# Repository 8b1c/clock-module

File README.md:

# clock-module

## Demo

https://github.com/user-attachments/assets/6f4d9207-cf31-4d4b-aec3-0dd87077b01e

## Clock Module Views

### Front View

### Back View

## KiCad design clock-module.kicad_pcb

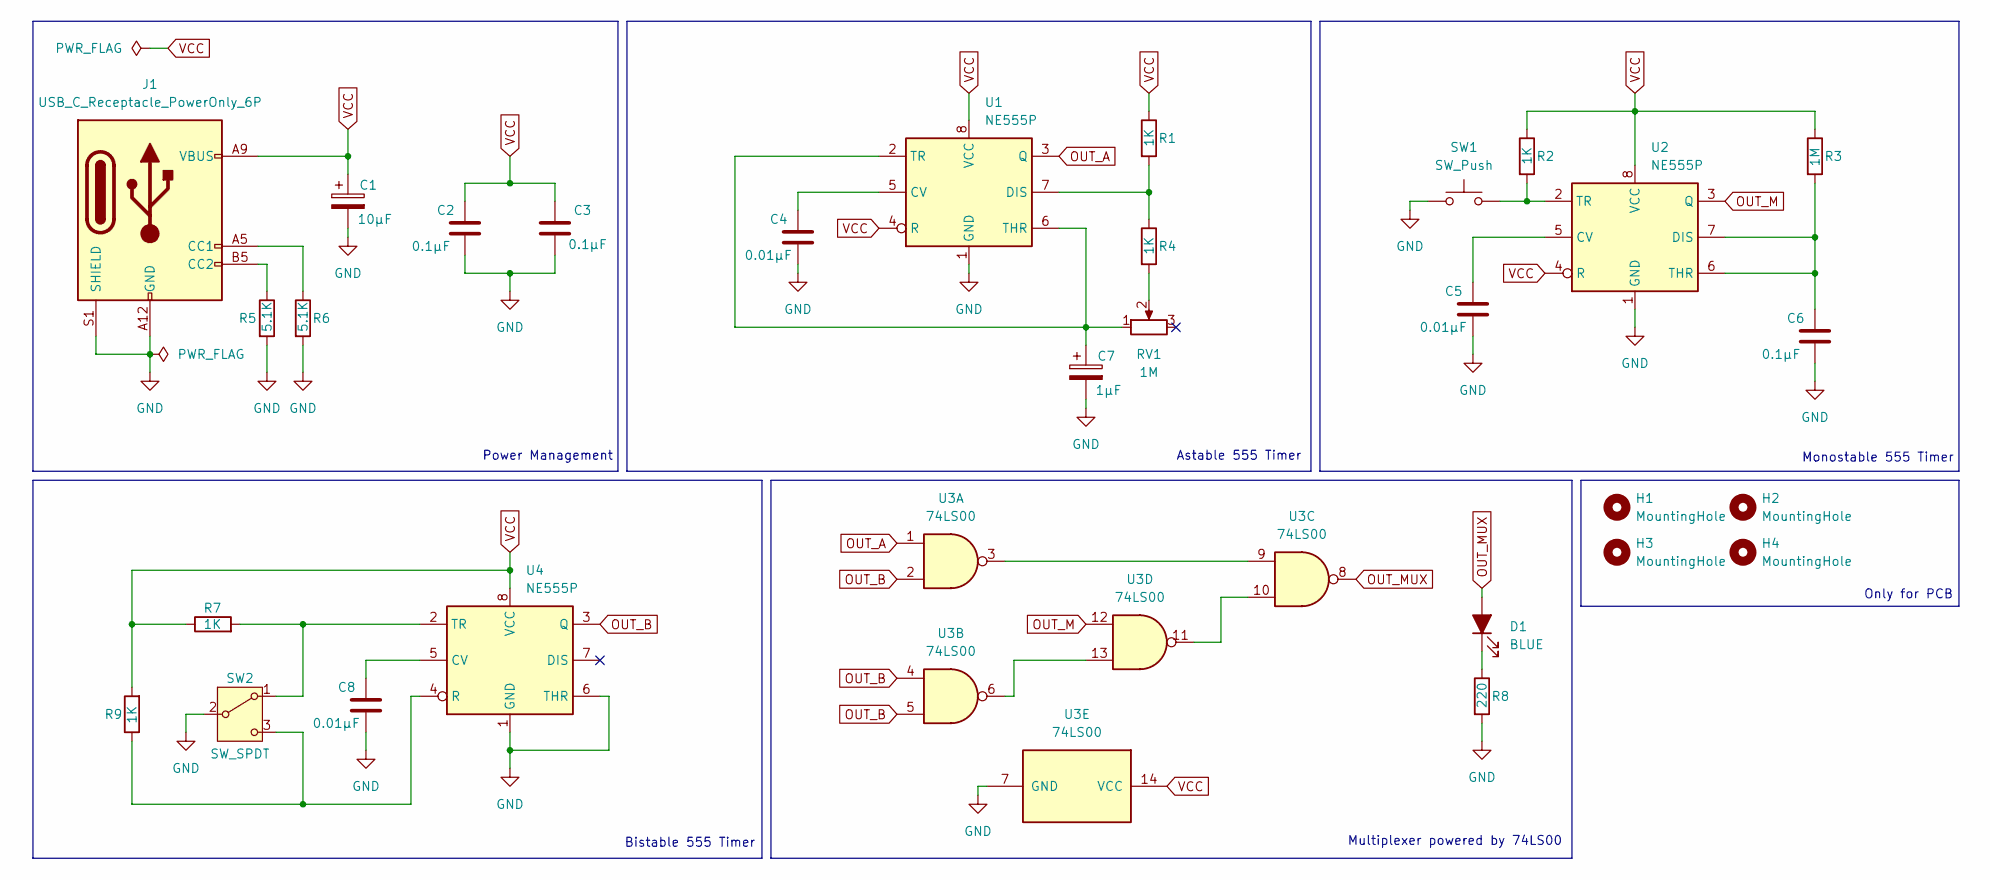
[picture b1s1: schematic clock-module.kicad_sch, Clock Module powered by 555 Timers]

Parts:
C1: 10µF; CP_Radial_D5.0mm_P2.00mm
C2, C3, C6: 0.1µF; C_Disc_D4.3mm_W1.9mm_P5.00mm
C4, C5, C8: 0.01µF; C_Disc_D4.3mm_W1.9mm_P5.00mm
C7: 1µF; CP_Radial_D5.0mm_P2.00mm
D1: BLUE; LED_D5.0mm
H1, H2, H3, H4: MountingHole; MountingHole_3.2mm_M3
J1: USB_C_Receptacle_PowerOnly_6P; USB_C_Receptacle_GCT_USB4135-GF-A_6P_TopMnt_Horizontal
R1, R2, R4, R7, R9: 1K; R_Axial_DIN0207_L6.3mm_D2.5mm_P7.62mm_Horizontal
R3: 1M; R_Axial_DIN0207_L6.3mm_D2.5mm_P7.62mm_Horizontal
R5, R6: 5.1K; R_Axial_DIN0207_L6.3mm_D2.5mm_P7.62mm_Horizontal
R8: 220; R_Axial_DIN0207_L6.3mm_D2.5mm_P7.62mm_Horizontal
RV1: 1M; Potentiometer_Bourns_PTV09A-1_Single_Vertical
SW1: SW_Push; SW_PUSH_6mm_H5mm
SW2: SW_SPDT; DPDT-pushbutton
U1, U2, U4: NE555P; DIP-8_W7.62mm
U3: 74LS00; DIP-14_W7.62mm

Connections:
GND: C1.2, C2.2, C3.2, C4.2, C5.2, C6.2, C7.2, C8.2, J1.A12 (GND), J1.B12 (GND), J1.S1 (SHIELD), R5.2, R6.2, R8.2, SW1.1, SW2.2 (B), U1.1 (GND), U2.1 (GND), U3.7 (GND), U4.1 (GND), U4.6 (THR)
unnamed: D1.1 (K), R8.1
unnamed: J1.A5 (CC1), R6.1
unnamed: J1.B5 (CC2), R5.1
unnamed: R4.2, RV1.2
unnamed: R7.2, SW2.1 (A), U4.2 (TR)
unnamed: R9.1, SW2.3 (C), U4.4 (R)
unnamed: C4.1, U1.5 (CV)
unnamed: R1.2, R4.1, U1.7 (DIS)
unnamed: C7.1, RV1.1, U1.2 (TR), U1.6 (THR)
unnamed: C5.1, U2.5 (CV)
unnamed: C6.1, R3.2, U2.6 (THR), U2.7 (DIS)
unnamed: R2.2, SW1.2, U2.2 (TR)
unnamed: U3.3, U3.9
unnamed: U3.10, U3.11
unnamed: U3.6, U3.13
unnamed: C8.1, U4.5 (CV)
OUT_A: U1.3 (Q), U3.1
OUT_B: U3.2, U3.4, U3.5, U4.3 (Q)
OUT_M: U2.3 (Q), U3.12
OUT_MUX: D1.2 (A), U3.8
VCC: C1.1, C2.1, C3.1, J1.A9 (VBUS), J1.B9 (VBUS), R1.1, R2.1, R3.1, R7.1, R9.2, U1.4 (R), U1.8 (VCC), U2.4 (R), U2.8 (VCC), U3.14 (VCC), U4.8 (VCC)

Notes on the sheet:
Power Management
Bistable 555 Timer
Only for PCB
Multiplexer powered by 74LS00
Monostable 555 Timer
Astable 555 Timer

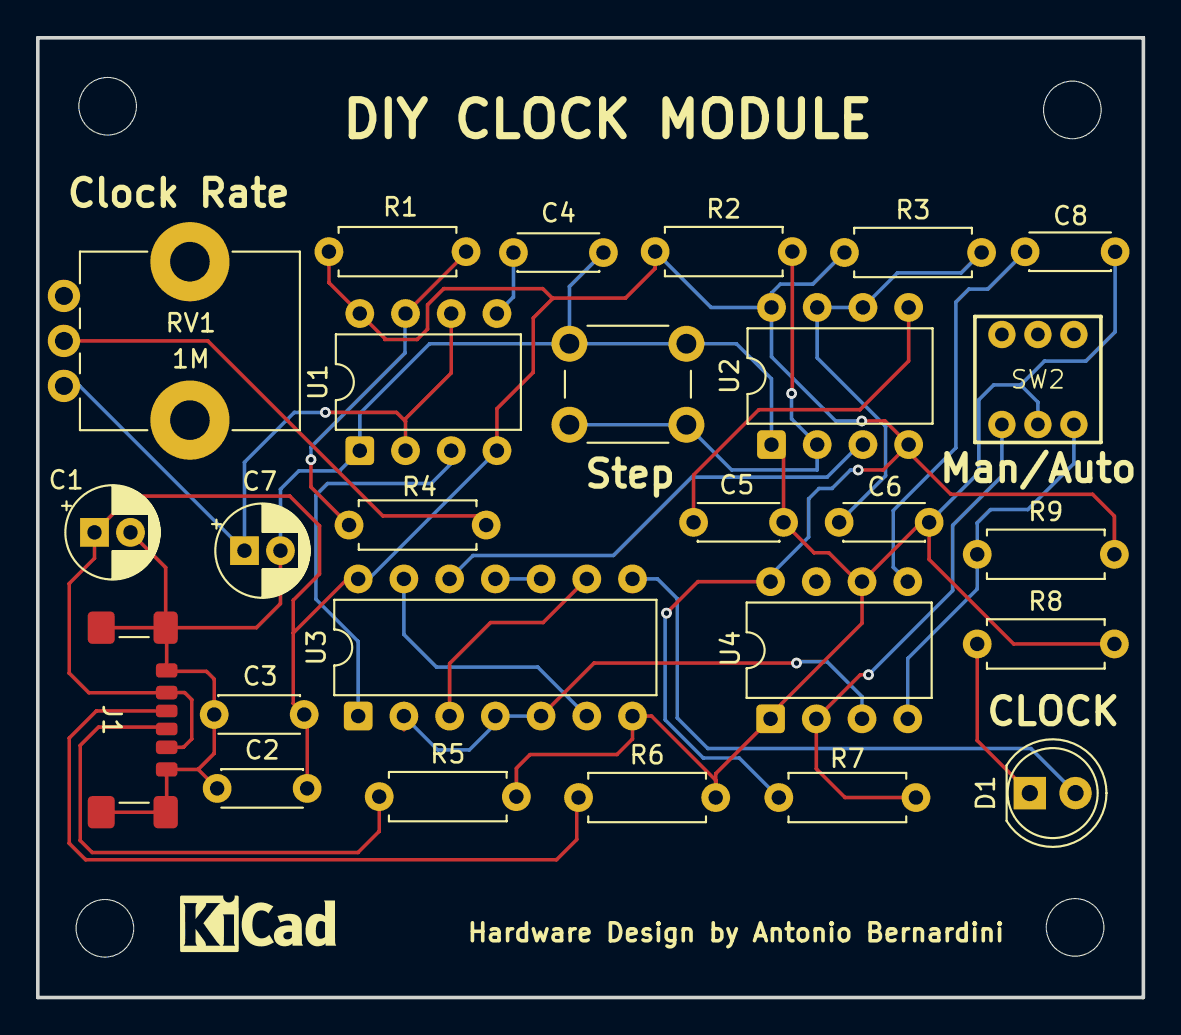
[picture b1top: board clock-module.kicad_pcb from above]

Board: 2 copper layers, 61.4 x 53.3 mm, 30 parts (0 on the bottom side), 22 nets.

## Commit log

2025-06-17 edited :zap:
2025-06-17 clock module project :tada:
2025-06-17 :fire:
2025-06-17 Linguist :zap:
2025-06-17 Gerber zip & pdf of schematic :tada:
2025-06-17 docs :zap:
2025-06-17 Added demo :tada:
